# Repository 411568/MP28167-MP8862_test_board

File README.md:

<h2>🧐 Features</h2>

PCB design for testing and comparison between MP28167/8862 DC/DC converter ICs with I2C connectivity.

<h2>🛡️ License:</h2>

This project is licensed under the MIT License.

<h2> 🙋‍♂️Authors </h2>

- Krzysztof Sikora

<h2>💖Like my work?</h2>

If you have any questions about the project feel free to contact us via email: krzysieksikora717@gmail.com

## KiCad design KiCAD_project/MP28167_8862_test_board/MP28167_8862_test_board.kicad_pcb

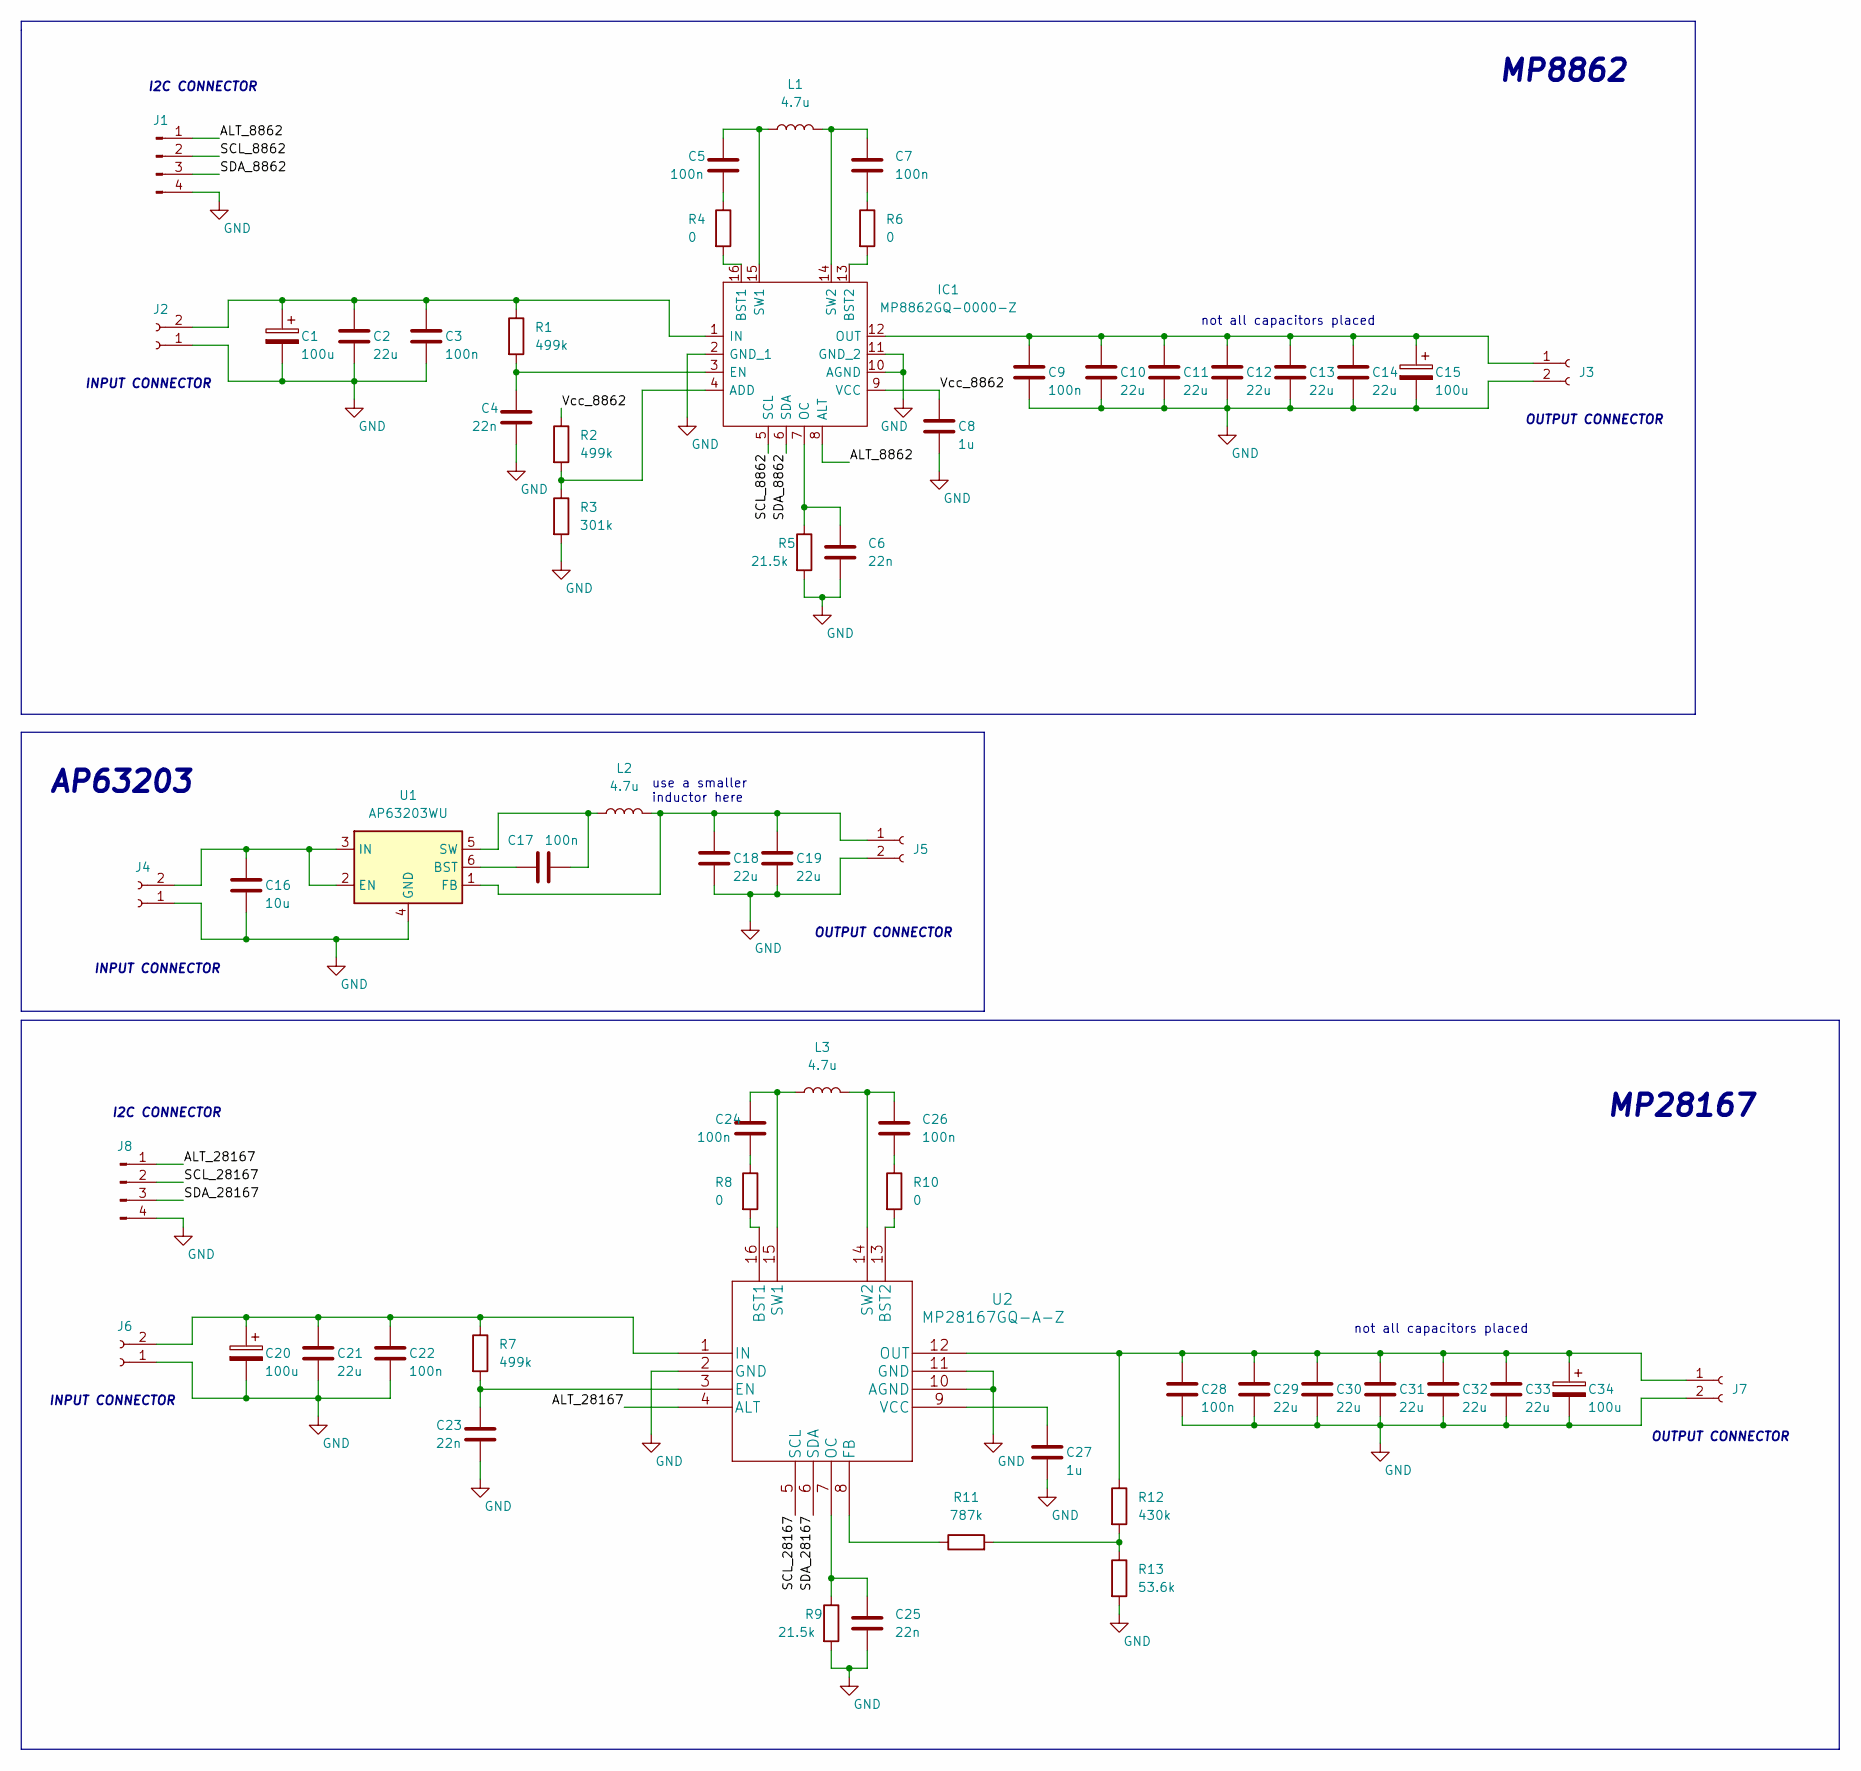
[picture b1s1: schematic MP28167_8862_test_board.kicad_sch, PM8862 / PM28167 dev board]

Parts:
C1, C15, C20, C34: 100u; CP_Elec_5x5.3
C2: 22u; C_0603_1608Metric_Pad1.08x0.95mm_HandSolder
C3, C5, C7, C9, C17, C24, C26: 100n; C_0805_2012Metric_Pad1.18x1.45mm_HandSolder
C4, C6, C23, C25: 22n; C_0603_1608Metric_Pad1.08x0.95mm_HandSolder
C8, C27: 1u; C_0603_1608Metric_Pad1.08x0.95mm_HandSolder
C10, C11, C12, C13, C14, C18, C19, C21, C29, C30, C31, C32, C33: 22u; C_0805_2012Metric_Pad1.18x1.45mm_HandSolder
C16: 10u; C_0805_2012Metric_Pad1.18x1.45mm_HandSolder
C22, C28: 100n; C_0603_1608Metric_Pad1.08x0.95mm_HandSolder
IC1: MP8862GQ-0000-Z; MP8862GQ; Manufacturer_Part_Number MP8862GQ-0000-Z; Mouser Part Number 946-MP8862GQ-0000-Z
J1, J8: Conn_01x04_Male; PinHeader_1x04_P2.54mm_Vertical
J2, J3, J4, J5, J6, J7: Conn_01x02_Female; SolderWire-0.1sqmm_1x02_P3.6mm_D0.4mm_OD1mm
L1, L3: 4.7u; EXL1V0705 inductor
L2: 4.7u; SDES064T-4R7MS inductor
R1, R2, R7: 499k; R_0603_1608Metric_Pad0.98x0.95mm_HandSolder
R3: 301k; R_0603_1608Metric_Pad0.98x0.95mm_HandSolder
R4, R6, R8, R10: 0; R_0603_1608Metric_Pad0.98x0.95mm_HandSolder
R5, R9: 21.5k; R_0603_1608Metric_Pad0.98x0.95mm_HandSolder
R11: 787k; R_0603_1608Metric_Pad0.98x0.95mm_HandSolder
R12: 430k; R_0603_1608Metric_Pad0.98x0.95mm_HandSolder
R13: 53.6k; R_0603_1608Metric_Pad0.98x0.95mm_HandSolder
U1: AP63203WU; TSOT-23-6
U2: MP28167GQ-A-Z

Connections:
/ALT_8862: IC1.8 (ALT), J1.1
/ALT_28167: J8.1, U2.4 (ALT)
/SCL_8862: IC1.5 (SCL), J1.2
/SCL_28167: J8.2, U2.5 (SCL)
/SDA_8862: IC1.6 (SDA), J1.3
/SDA_28167: J8.3, U2.6 (SDA)
/Vcc_8862: C8.1, IC1.9 (VCC), R2.1
GND: C1.2, C2.2, C3.2, C4.2, C6.2, C8.2, C9.2, C10.2, C11.2, C12.2, C13.2, C14.2, C15.2, C16.2, C18.2, C19.2, C20.2, C21.2, C22.2, C23.2, C25.2, C27.2, C28.2, C29.2, C30.2, C31.2, C32.2, C33.2, C34.2, IC1.2 (GND_1), IC1.10 (AGND), IC1.11 (GND_2), J1.4, J2.1, J3.2, J4.1, J5.2, J6.1, J7.2, J8.4, R3.2, R5.2, R9.2, R13.2, U1.4 (GND), U2.2 (GND), U2.10 (AGND), U2.11 (GND)
unnamed: C1.1, C2.1, C3.1, IC1.1 (IN), J2.2, R1.1
unnamed: C4.1, IC1.3 (EN), R1.2
unnamed: C5.1, IC1.15 (SW1), L1.1
unnamed: C5.2, R4.1
unnamed: C6.1, IC1.7 (OC), R5.1
unnamed: C7.1, IC1.14 (SW2), L1.2
unnamed: C7.2, R6.1
unnamed: C9.1, C10.1, C11.1, C12.1, C13.1, C14.1, C15.1, IC1.12 (OUT), J3.1
unnamed: C16.1, J4.2, U1.2 (EN), U1.3 (IN)
unnamed: C17.1, U1.6 (BST)
unnamed: C17.2, L2.1, U1.5 (SW)
unnamed: C18.1, C19.1, J5.1, L2.2, U1.1 (FB)
unnamed: C20.1, C21.1, C22.1, J6.2, R7.1, U2.1 (IN)
unnamed: C23.1, R7.2, U2.3 (EN)
unnamed: C24.1, L3.1, U2.15 (SW1)
unnamed: C24.2, R8.1
unnamed: C25.1, R9.1, U2.7 (OC)
unnamed: C26.1, L3.2, U2.14 (SW2)
unnamed: C26.2, R10.1
unnamed: C27.1, U2.9 (VCC)
unnamed: C28.1, C29.1, C30.1, C31.1, C32.1, C33.1, C34.1, J7.1, R12.1, U2.12 (OUT)
unnamed: IC1.4 (ADD), R2.2, R3.1
unnamed: IC1.13 (BST2), R6.2
unnamed: IC1.16 (BST1), R4.2
unnamed: R8.2, U2.16 (BST1)
unnamed: R10.2, U2.13 (BST2)
unnamed: R11.1, U2.8 (FB)
unnamed: R11.2, R12.2, R13.1

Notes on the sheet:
OUTPUT CONNECTOR
MP8862
not all capacitors placed
AP63203
MP28167
use a smaller inductor here
INPUT CONNECTOR
I2C CONNECTOR

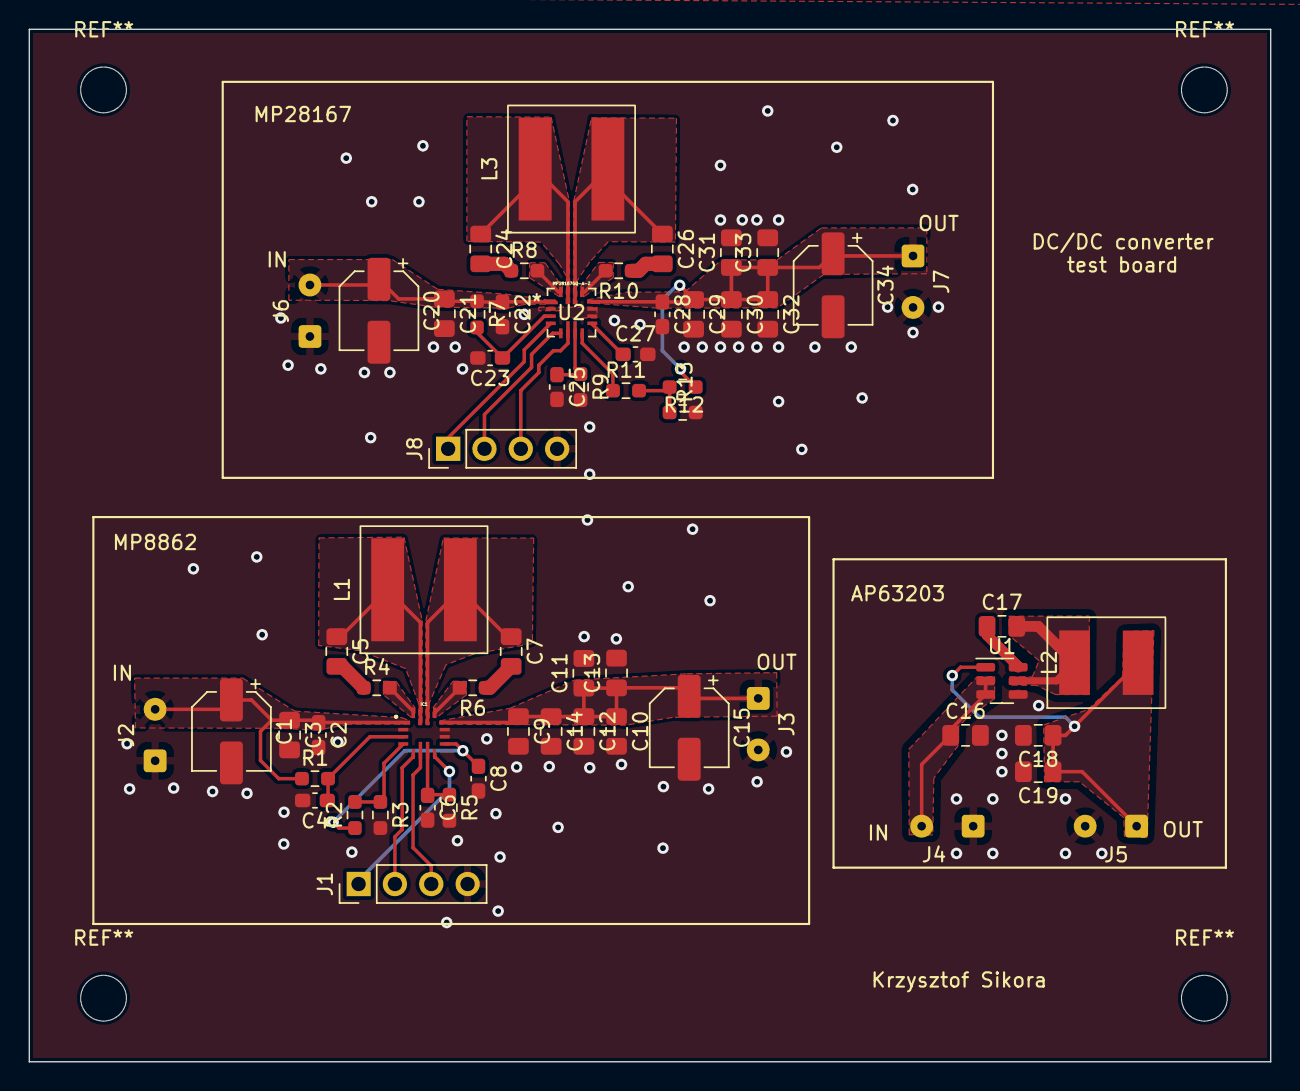
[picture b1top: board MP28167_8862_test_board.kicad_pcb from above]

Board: 2 copper layers, 86.8 x 72.2 mm, 61 parts (0 on the bottom side), 36 nets.

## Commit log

2023-03-09 schematic update
2023-03-10 first schematic
2023-03-10 footprint update
2023-03-12 pcb layout update
2023-03-12 readme update
2025-01-30 Create LICENSE
